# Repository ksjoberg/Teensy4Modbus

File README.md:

# Teensy4Modbus

This application uses the CDC-ECM mode implemented in the Teensy Cores fork at https://github.com/ksjoberg/cores/tree/teensy4-ecm to expose the Teensy as a network device to a computer.

The vision is to add a ModbusTCP listener so that the Teensy can act as a ModbusTCP to ModbusRTU gateway using one or more of its seven hardware serial ports.

The inspiration sprung out of the fact that PyModbus can't properly participate on a Modbus serial bus with the RTU protocol: the framing information is lost as the serial port exposes the bus as a stream of bytes. The RTU frames are defined as being preceeded by a 3.5 char time silence on the bus, but the usermode applications usually just calls the serial port read function to to fill a provided buffer. This read call bridges the inter-frame bus silence and may returns multiple partial frames in one read.

ModbusTCP handles the framing correctly, so if PyModbus can talk to a ModbusTCP device instead it will work as intended.

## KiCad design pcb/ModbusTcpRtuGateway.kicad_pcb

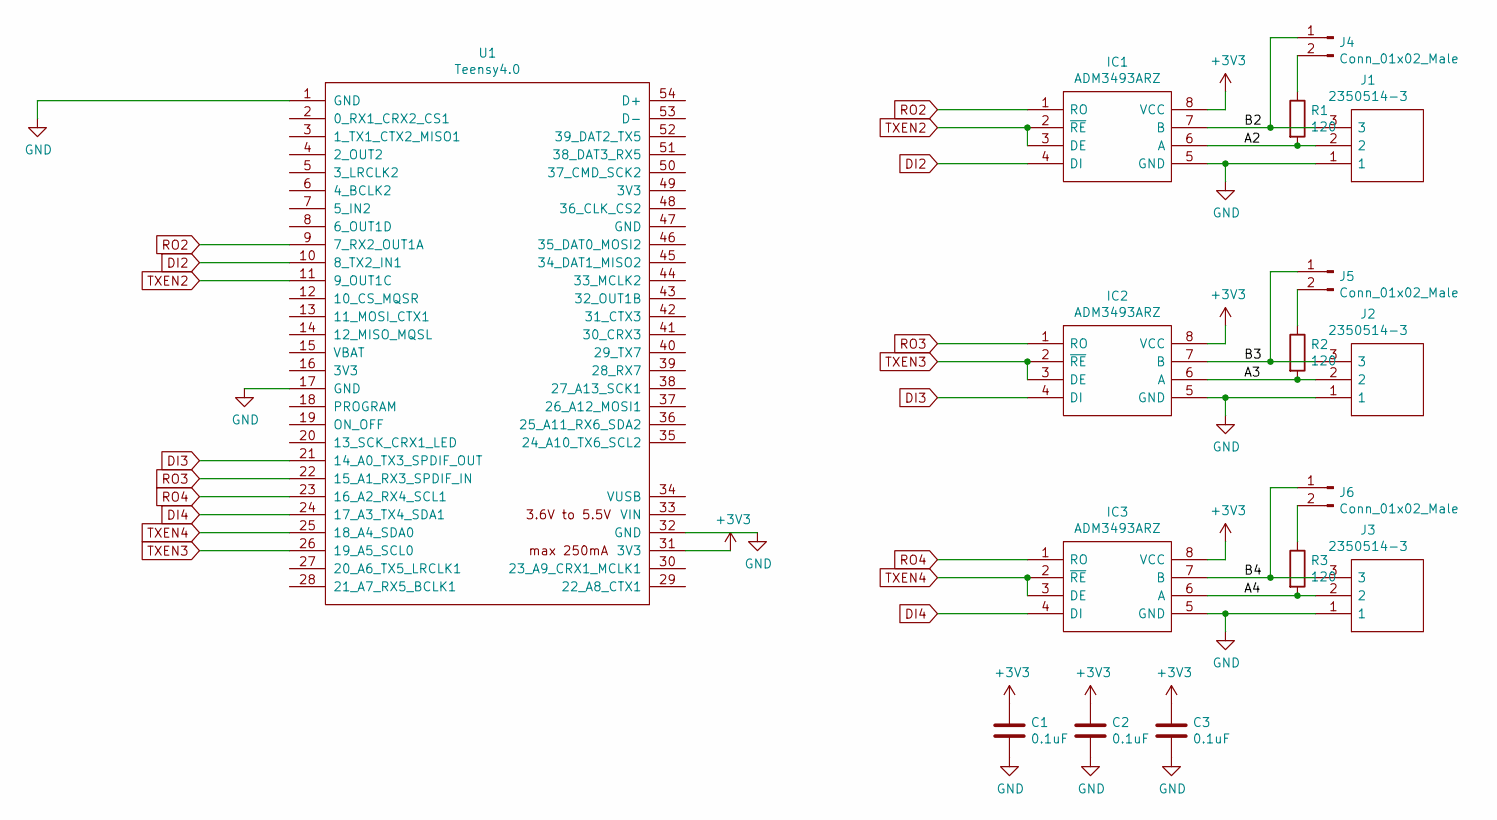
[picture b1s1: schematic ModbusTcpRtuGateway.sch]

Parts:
C1, C2, C3: 0.1uF; C_0805_2012Metric_Pad1.18x1.45mm_HandSolder
IC1, IC2, IC3: ADM3493ARZ; SOIC127P600X175-8N; Mouser Part Number 584-ADM3493ARZ
J1, J2, J3: 2350514-3; SHDRRA3W90P0X350_1X3_1110X920X691P; Manufacturer_Part_Number 2350514-3; Mouser Part Number 571-2350514-3
J4, J5, J6: Conn_01x02_Male; PinHeader_1x02_P2.54mm_Vertical
R1, R2, R3: 120; R_0603_1608Metric_Pad0.98x0.95mm_HandSolder
U1: Teensy4.0; Teensy40

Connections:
+3V3: C1.1, C2.1, C3.1, IC1.8 (VCC), IC2.8 (VCC), IC3.8 (VCC), U1.31 (3V3)
/A2: IC1.6 (A), J1.2, R1.2
/A3: IC2.6 (A), J2.2, R2.2
/A4: IC3.6 (A), J3.2, R3.2
/B2: IC1.7 (B), J1.3, J4.1
/B3: IC2.7 (B), J2.3, J5.1
/B4: IC3.7 (B), J3.3, J6.1
DI2: IC1.4 (DI), U1.10 (8_TX2_IN1)
DI3: IC2.4 (DI), U1.21 (14_A0_TX3_SPDIF_OUT)
DI4: IC3.4 (DI), U1.24 (17_A3_TX4_SDA1)
GND: C1.2, C2.2, C3.2, IC1.5 (GND), IC2.5 (GND), IC3.5 (GND), J1.1, J2.1, J3.1, U1.1 (GND), U1.17 (GND), U1.32 (GND)
unnamed: J4.2, R1.1
unnamed: J5.2, R2.1
unnamed: J6.2, R3.1
RO2: IC1.1 (RO), U1.9 (7_RX2_OUT1A)
RO3: IC2.1 (RO), U1.22 (15_A1_RX3_SPDIF_IN)
RO4: IC3.1 (RO), U1.23 (16_A2_RX4_SCL1)
TXEN2: IC1.2 (~RE), IC1.3 (DE), U1.11 (9_OUT1C)
TXEN3: IC2.2 (~RE), IC2.3 (DE), U1.26 (19_A5_SCL0)
TXEN4: IC3.2 (~RE), IC3.3 (DE), U1.25 (18_A4_SDA0)

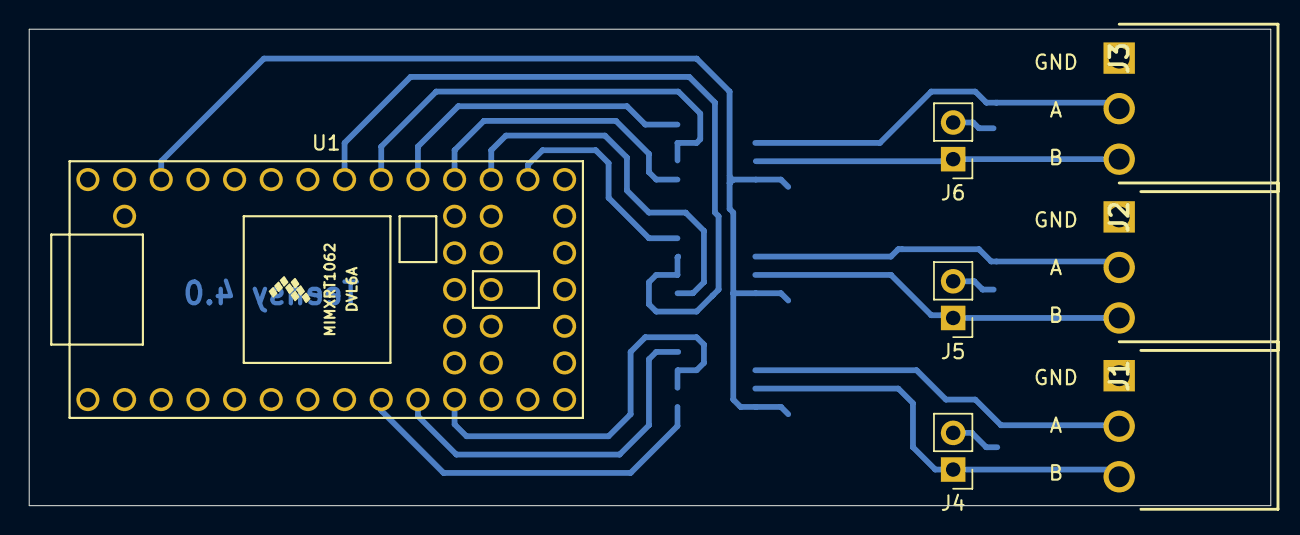
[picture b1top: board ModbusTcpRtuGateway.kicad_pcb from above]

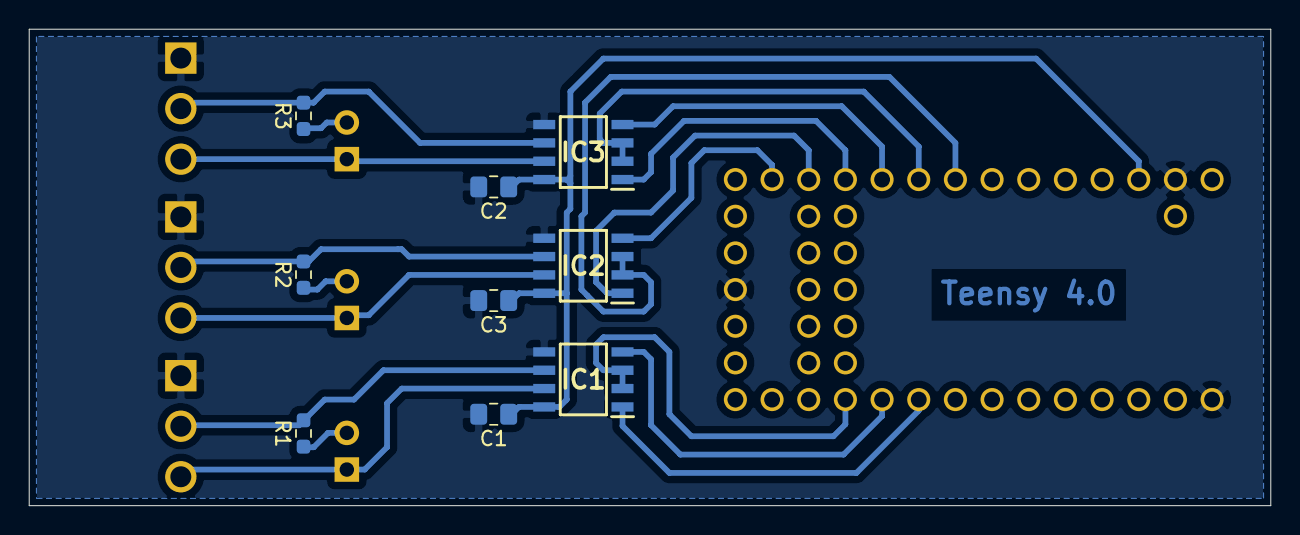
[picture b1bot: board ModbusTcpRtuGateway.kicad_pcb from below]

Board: 2 copper layers, 86.0 x 33.0 mm, 16 parts (9 on the bottom side), 20 nets.

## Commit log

2021-10-11 Initial CDC-ECM application
2021-10-21 Cleanup
2021-10-21 Add RTU slave capability
2021-10-24 Align pins with HW update
2021-10-28 PCB initial (no submodule)
2021-11-02 Add support for DHCP renew
2022-03-16 Code cleanup
